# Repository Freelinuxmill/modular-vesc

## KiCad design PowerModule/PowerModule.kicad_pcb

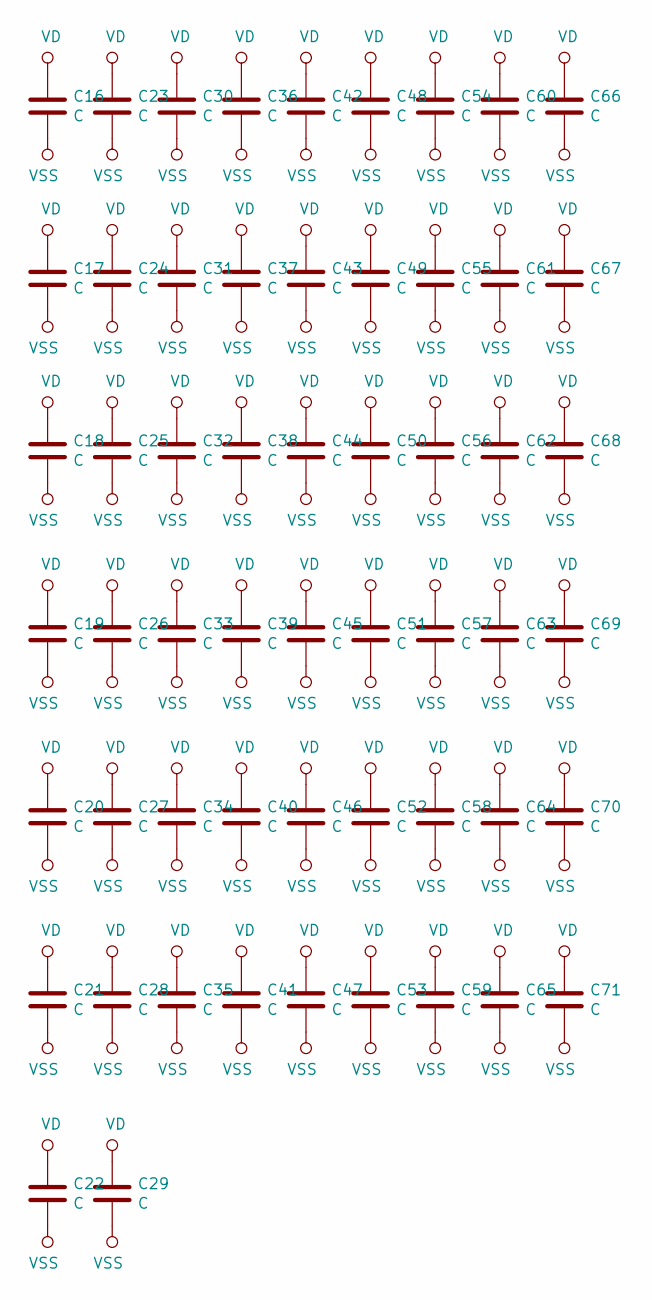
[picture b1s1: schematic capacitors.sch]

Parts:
C16, C17, C18, C19, C20, C21, C22, C23, C24, C25, C26, C27, C28, C29, C30, C31, C32, C33, C34, C35, C36, C37, C38, C39, C40, C41, C42, C43, C44, C45, C46, C47, C48, C49, C50, C51, C52, C53, C54, C55, C56, C57, C58, C59, C60, C61, C62, C63, C64, C65, C66, C67, C68, C69, C70, C71: C; C_0805_2012Metric

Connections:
VD: C16.1, C17.1, C18.1, C19.1, C20.1, C21.1, C22.1, C23.1, C24.1, C25.1, C26.1, C27.1, C28.1, C29.1, C30.1, C31.1, C32.1, C33.1, C34.1, C35.1, C36.1, C37.1, C38.1, C39.1, C40.1, C41.1, C42.1, C43.1, C44.1, C45.1, C46.1, C47.1, C48.1, C49.1, C50.1, C51.1, C52.1, C53.1, C54.1, C55.1, C56.1, C57.1, C58.1, C59.1, C60.1, C61.1, C62.1, C63.1, C64.1, C65.1, C66.1, C67.1, C68.1, C69.1, C70.1, C71.1; also elsewhere on the board
VSS: C16.2, C17.2, C18.2, C19.2, C20.2, C21.2, C22.2, C23.2, C24.2, C25.2, C26.2, C27.2, C28.2, C29.2, C30.2, C31.2, C32.2, C33.2, C34.2, C35.2, C36.2, C37.2, C38.2, C39.2, C40.2, C41.2, C42.2, C43.2, C44.2, C45.2, C46.2, C47.2, C48.2, C49.2, C50.2, C51.2, C52.2, C53.2, C54.2, C55.2, C56.2, C57.2, C58.2, C59.2, C60.2, C61.2, C62.2, C63.2, C64.2, C65.2, C66.2, C67.2, C68.2, C69.2, C70.2, C71.2; also elsewhere on the board

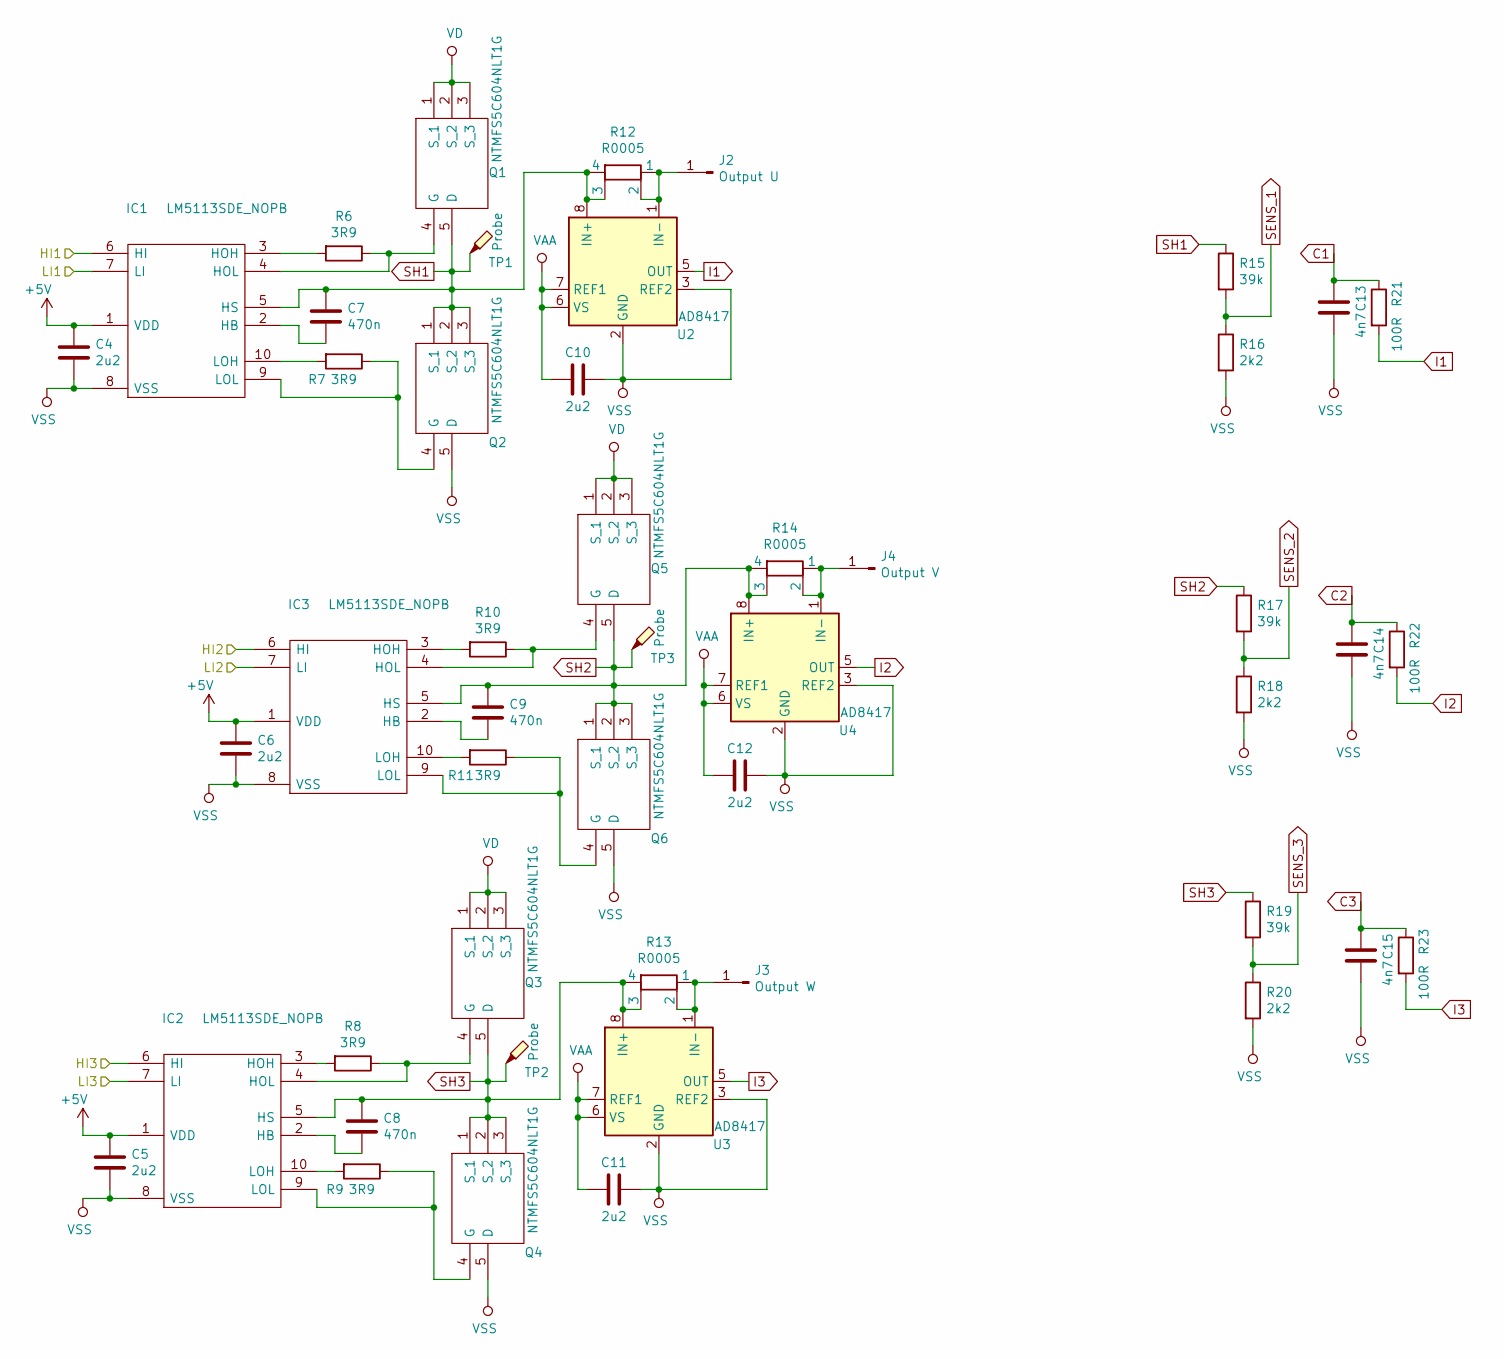
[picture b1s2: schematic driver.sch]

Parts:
C4, C5, C6, C10, C11, C12: 2u2; C_0603_1608Metric
C7, C8, C9: 470n; C_0603_1608Metric
C13, C14, C15: 4n7; C_0603_1608Metric
IC1, IC2, IC3: LM5113SDE_NOPB; SON80P400X400X80-11N; Mouser Part Number 926-LM5113SDE/NOPB
J2: Output U; Pad_Output
J3: Output W; Pad_Output
J4: Output V; Pad_Output
Q1, Q2, Q3, Q4, Q5, Q6: NTMFS5C604NLT1G; DFN5_5X6(SO-8FL)_CASE-488AA_ISSUE_M-1; Mouser Part Number 863-NTMFS5C604NLT1G
R6, R7, R8, R9, R10, R11: 3R9; R_0603_1608Metric
R12, R13, R14: R0005
R15, R17, R19: 39k; R_0603_1608Metric
R16, R18, R20: 2k2; R_0603_1608Metric
R21, R22, R23: 100R; R_0603_1608Metric
TP1, TP2, TP3: Probe; TestPoint_THTPad_D1.0mm_Drill0.5mm
U2, U3, U4: AD8417

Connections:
+5V: C4.2, C5.2, C6.2, IC1.1 (VDD), IC2.1 (VDD), IC3.1 (VDD); also elsewhere on the board
/HI1: IC1.6 (HI); also elsewhere on the board
/HI2: IC3.6 (HI); also elsewhere on the board
/HI3: IC2.6 (HI); also elsewhere on the board
/LI1: IC1.7 (LI); also elsewhere on the board
/LI2: IC3.7 (LI); also elsewhere on the board
/LI3: IC2.7 (LI); also elsewhere on the board
C1: C13.2, R21.1; also elsewhere on the board
C2: C14.2, R22.1; also elsewhere on the board
C3: C15.2, R23.1; also elsewhere on the board
I1: R21.2, U2.5 (OUT)
I2: R22.2, U4.5 (OUT)
I3: R23.2, U3.5 (OUT)
unnamed: C7.1, IC1.2 (HB)
unnamed: C8.1, IC2.2 (HB)
unnamed: C9.1, IC3.2 (HB)
unnamed: IC1.3 (HOH), R6.2
unnamed: IC1.4 (HOL), Q1.4 (G), R6.1
unnamed: IC1.9 (LOL), Q2.4 (G), R7.1
unnamed: IC1.10 (LOH), R7.2
unnamed: IC2.3 (HOH), R8.2
unnamed: IC2.4 (HOL), Q3.4 (G), R8.1
unnamed: IC2.9 (LOL), Q4.4 (G), R9.1
unnamed: IC2.10 (LOH), R9.2
unnamed: IC3.3 (HOH), R10.2
unnamed: IC3.4 (HOL), Q5.4 (G), R10.1
unnamed: IC3.9 (LOL), Q6.4 (G), R11.1
unnamed: IC3.10 (LOH), R11.2
unnamed: J2.1, R12.1, R12.2, U2.1 (IN-)
unnamed: J3.1, R13.1, R13.2, U3.1 (IN-)
unnamed: J4.1, R14.1, R14.2, U4.1 (IN-)
SENS_1: R15.2, R16.1; also elsewhere on the board
SENS_2: R17.2, R18.1; also elsewhere on the board
SENS_3: R19.2, R20.1; also elsewhere on the board
SH1: C7.2, IC1.5 (HS), Q1.5 (D), Q2.1 (S_1), Q2.2 (S_2), Q2.3 (S_3), R12.3, R12.4, R15.1, TP1.1, U2.8 (IN+)
SH2: C9.2, IC3.5 (HS), Q5.5 (D), Q6.1 (S_1), Q6.2 (S_2), Q6.3 (S_3), R14.3, R14.4, R17.1, TP3.1, U4.8 (IN+)
SH3: C8.2, IC2.5 (HS), Q3.5 (D), Q4.1 (S_1), Q4.2 (S_2), Q4.3 (S_3), R13.3, R13.4, R19.1, TP2.1, U3.8 (IN+)
VAA: C10.2, C11.2, C12.2, U2.6 (VS), U2.7 (REF1), U3.6 (VS), U3.7 (REF1), U4.6 (VS), U4.7 (REF1); also elsewhere on the board
VD: Q1.1 (S_1), Q1.2 (S_2), Q1.3 (S_3), Q3.1 (S_1), Q3.2 (S_2), Q3.3 (S_3), Q5.1 (S_1), Q5.2 (S_2), Q5.3 (S_3); also elsewhere on the board
VSS: C4.1, C5.1, C6.1, C10.1, C11.1, C12.1, C13.1, C14.1, C15.1, IC1.8 (VSS), IC2.8 (VSS), IC3.8 (VSS), Q2.5 (D), Q4.5 (D), Q6.5 (D), R16.2, R18.2, R20.2, U2.2 (GND), U2.3 (REF2), U3.2 (GND), U3.3 (REF2), U4.2 (GND), U4.3 (REF2); also elsewhere on the board

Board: 2 copper layers, 109 parts (3 on the bottom side), 39 nets, no tracks yet.

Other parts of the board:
C1: 2u2; C_0603_1608Metric
C2: 220nF; C_0603_1608Metric
D1: PMEG6020AELR; D_SOD-123
J1: SlimstackStecker; 2039550201
L1: 74438335220; L_Wuerth_MAPI-3015
R1: 100k; R_0603_1608Metric
R2: 10k; R_0603_1608Metric
R3: 54k9; R_0603_1608Metric
R4: 39K; R_0603_1608Metric
R5: 2k2; R_0603_1608Metric
U1: LMR16006YDDCT; SOT-23-6

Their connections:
+5V: J1.1, L1.2, R3.1; also elsewhere on the board
/HI1: J1.5; also elsewhere on the board
/HI2: J1.6; also elsewhere on the board
/HI3: J1.7; also elsewhere on the board
/LI1: J1.8; also elsewhere on the board
/LI2: J1.9; also elsewhere on the board
/LI3: J1.10; also elsewhere on the board
C1: J1.11; also elsewhere on the board
C2: J1.12; also elsewhere on the board
C3: J1.13; also elsewhere on the board
unnamed: C2.1, U1.1
unnamed: C2.2, D1.1, L1.1, U1.6
unnamed: R1.2, U1.4
unnamed: R2.1, R3.2, U1.3
SENS_1: J1.2; also elsewhere on the board
SENS_2: J1.3; also elsewhere on the board
SENS_3: J1.4; also elsewhere on the board
SENS_SUPPLY: J1.19, R4.2, R5.1
VAA: J1.18; also elsewhere on the board
VD: C1.1, R1.1, R4.1, U1.5; also elsewhere on the board
VSS: C1.2, D1.2, J1.20, R2.2, R5.2, U1.2; also elsewhere on the board
